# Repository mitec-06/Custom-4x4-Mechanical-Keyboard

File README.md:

# Custom 4x4 Keyboard PCB Design

This project is a custom 4x4 mechanical keyboard PCB featuring USB HID firmware on RP2040, addressable RGB LEDs (SK6812) driven via PIO state machine, rotary encoder brightness control, and HSV color animation functions.

## Functions

### Core Functions

- 16 keys arranged in a 4 x 4 matrix pattern.

- 6 key rollover - up to 6 simultaneous keypresses registered.

- USB HID keyboard output - It can work as a plug-and-play keyboard on any computer.

- Debouncing key detection - Prevents false or double triggers from a mechanical switch bounce.

- Diode per key - Diodes were included for every key in order to prevent ghosting.

### LED Functions
- Idle RGB ripple animation - Outward ripple effect starting from center rings cycling through the entire HSV color spectrum.

- Keypress-reactive LEDS - Animation switches to keypress mode when any key is pressed, returns to idle afterwards.

- Full HSV color transition - Smooth transition between red, orange, yellow, green, cyan, blue, magenta and back.

- Ring based animation - Three concentric rings with slight phase offset creating a ripple appearance.

- Brightness control - Using a rotary encoder, smooth brightness scaling from 0-100% applied uniformly to all LEDs.

- Brightness preserved across all animation modes, whether its idle or a key is being pressed.

### Encoder Functions 

- Clockwise rotation increases brightness, counterclockwise rotation decreases brightness.

- Hardware debouncing edge detection - Prevents any skips when rotating the encoder.

### Hardware Features 

- 3.3V to 5V level shifting for LED data signal via SN74LV1T34

- Daisy-chained SK6812 MINI-E LEDs driven via RP2040 PIO state machine.

- RP2040 PIO state machine - Dedicated programmable Input/Output handles precise WS2812 timing independent of CPU timing.

- WS2812 protocol followed to ensure correct latch reset timing.

- USB powered - single cable for both HID and power communication.

## Timeline

### April 2026 - May 2026

Primarily worked on keyboard research, and drafting the schematic and pcb. Once the pcb was finished, spent some time revising the placement of parts on the board to make sure that there were no shorts or awkward placements that would make assembly difficult.

### May 2026 - June 2026

Ordered the first batch of PCBs from PCBWay, and begun soldering the first prototype, however several hardware bugs prevented the LEDs from functioning properly, causing odd behavior, and allowing only the typing to work.

### June 2026 - July 2026
Managed to get the first four LEDs of the board working, with the other 12 not functioning properly.

Extensively debugged several iterations of the board, ultimately finding that the DIN and DOUT pins on the SK6812 MINI-Es were swapped on the 5th-8th LEDs.

Because the keyboard follows a serpentine transmission of data where the signal of the next LED depends on the signal of the last LED, this broke the sequence for the rest of the LEDs.

Ultimately, the DIN/DOUT pins were finally oriented correctly, and a new batch of PCBs were ordered.

### July 2026 - August 2026

Assembled and soldered the new functioning PCBs, which finally had all 16 LEDs turn on properly. In this time period, the rest of the firmware was added, including the logic for the HSV color transition, the ring-like HSV color animation, the logic for the LED brightness dimming, etc.

In this time period, the case of the PCB was modelled using OnShape, and 3D printed, being assembled towards the end of this project, and ultimately yielding the final keyboard product. :)

## Future Improvements

- Most notably, while assembling/soldering check more frequently whether the parts assembled have the right voltage/behavior using tools such as oscilloscopes or multimeters.

- When hardware debugging, record previous symptoms of the build to ensure that the user assembling the PCB has the full picture, and might not confuse the actual cause of the bug for something else.

- Exercise more caution right before ordering PCBs, ensuring several times that the parts on the PCB have been wired correctly, even if it may pass the Design Rule Check.

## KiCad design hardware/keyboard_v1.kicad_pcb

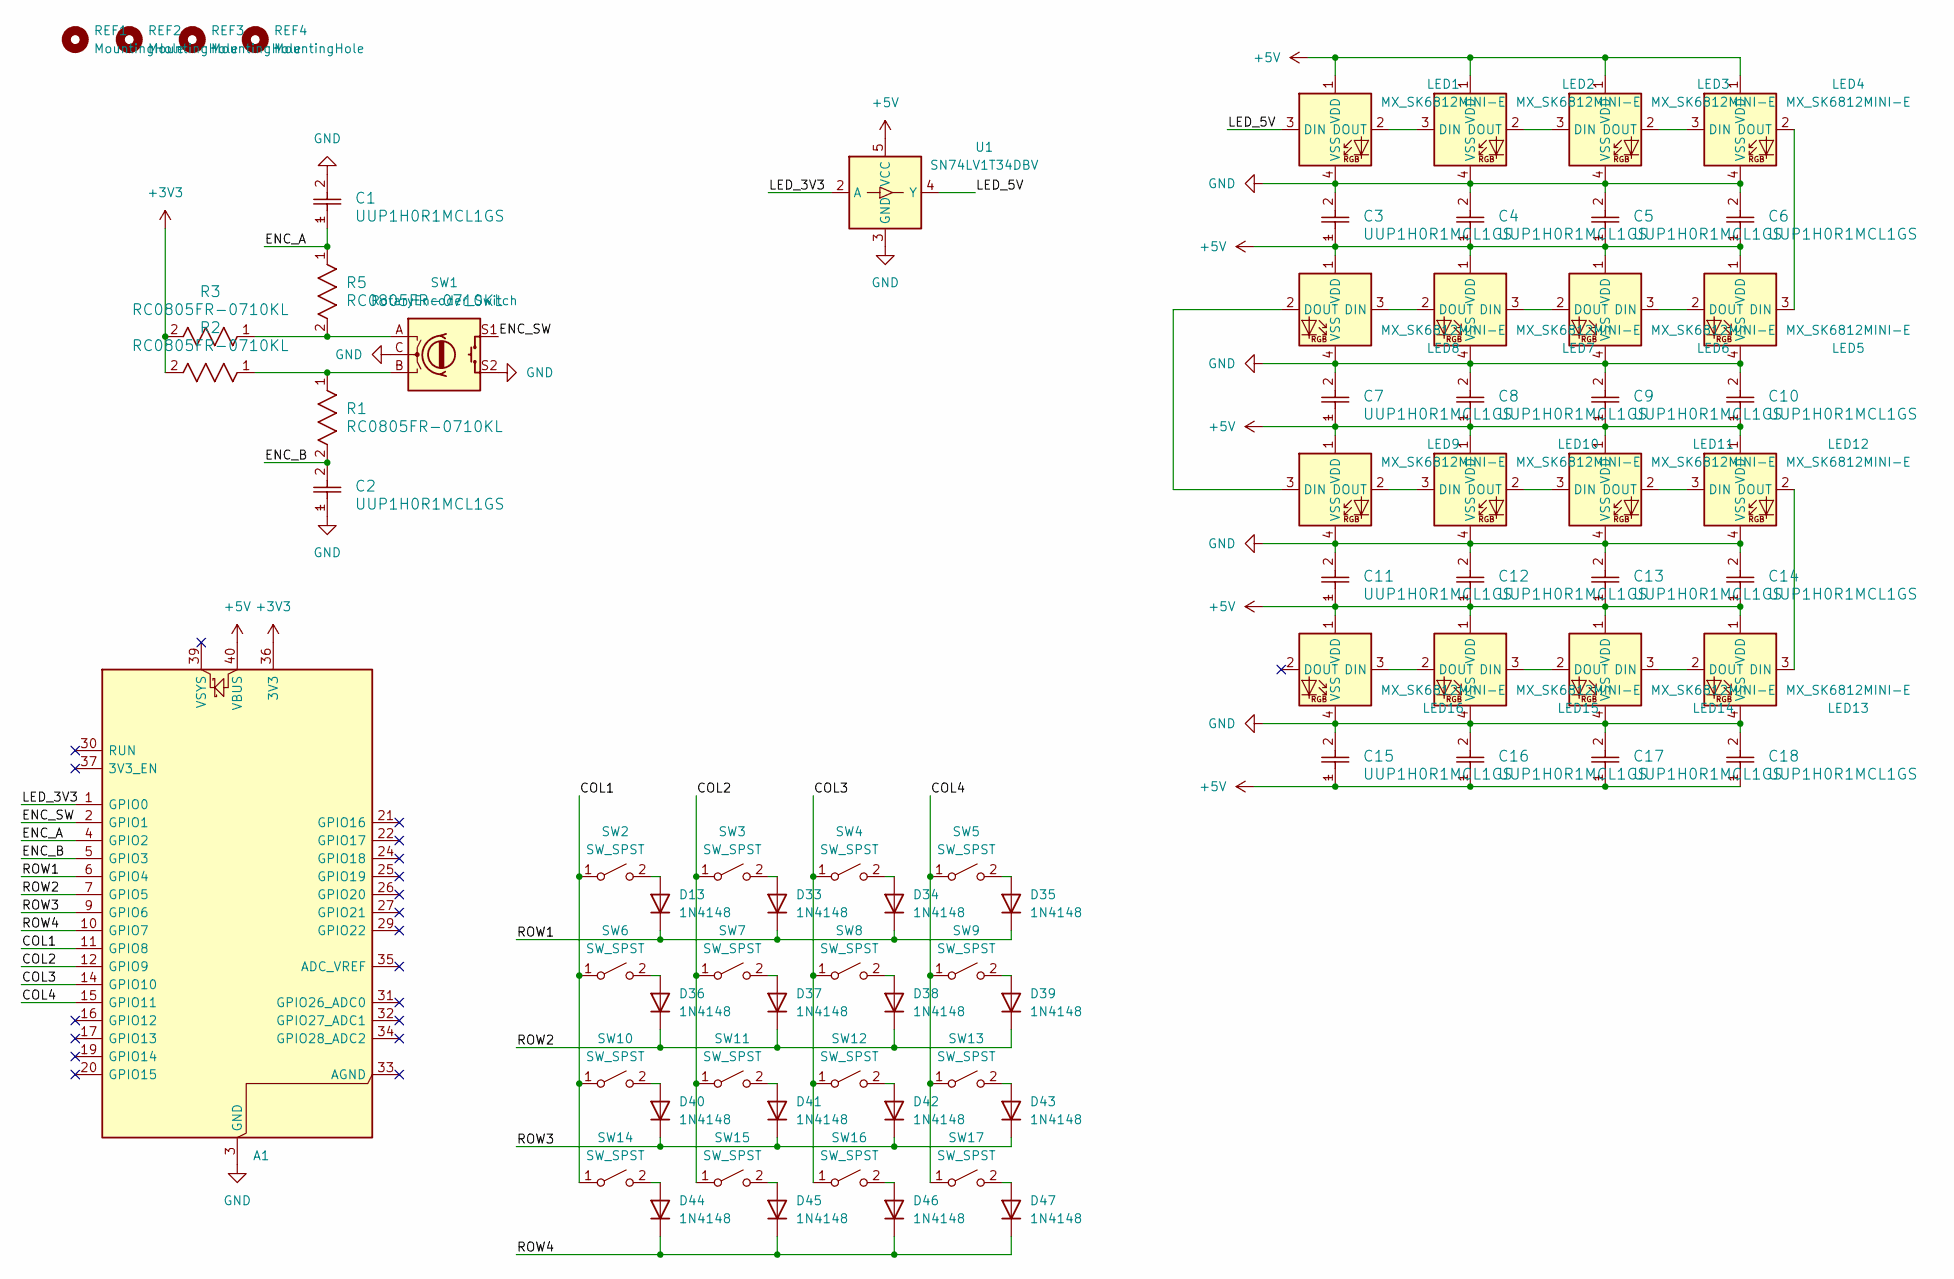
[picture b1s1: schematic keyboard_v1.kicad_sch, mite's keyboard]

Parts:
A1: RaspberryPi_Pico; RaspberryPi_Pico_Common_Unspecified
C1, C2, C3, C4, C5, C6, C7, C8, C9, C10, C11, C12, C13, C14, C15, C16, C17, C18: UUP1H0R1MCL1GS; CAP_UCD_4X5P8_NCH
D13, D33, D34, D35, D36, D37, D38, D39, D40, D41, D42, D43, D44, D45, D46, D47: 1N4148; D_DO-35_SOD27_P7.62mm_Horizontal
LED1, LED2, LED3, LED4, LED5, LED6, LED7, LED8, LED9, LED10, LED11, LED12, LED13, LED14, LED15, LED16: MX_SK6812MINI-E; LED_MX_6028R
R1, R2, R3, R5: RC0805FR-0710KL; RC0805N_YAG
REF1, REF2, REF3, REF4: MountingHole; MountingHole_3.2mm_M3
SW1: RotaryEncoder_Switch; RotaryEncoder_Alps_EC11E-Switch_Vertical_H20mm
SW2, SW3, SW4, SW5, SW6, SW7, SW8, SW9, SW10, SW11, SW12, SW13, SW14, SW15, SW16, SW17: SW_SPST; SW_Cherry_MX_1.00u_PCB
U1: SN74LV1T34DBV; SOT-23-5

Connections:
+3V3: A1.36 (3V3), R2.2, R3.2
+5V: A1.40 (VBUS), C3.1, C4.1, C5.1, C6.1, C7.1, C8.1, C9.1, C10.1, C11.1, C12.1, C13.1, C14.1, C15.1, C16.1, C17.1, C18.1, LED1.1 (VDD), LED2.1 (VDD), LED3.1 (VDD), LED4.1 (VDD), LED5.1 (VDD), LED6.1 (VDD), LED7.1 (VDD), LED8.1 (VDD), LED9.1 (VDD), LED10.1 (VDD), LED11.1 (VDD), LED12.1 (VDD), LED13.1 (VDD), LED14.1 (VDD), LED15.1 (VDD), LED16.1 (VDD), U1.5 (VCC)
/COL1: A1.11 (GPIO8), SW2.1 (A), SW6.1 (A), SW10.1 (A), SW14.1 (A)
/COL2: A1.12 (GPIO9), SW3.1 (A), SW7.1 (A), SW11.1 (A), SW15.1 (A)
/COL3: A1.14 (GPIO10), SW4.1 (A), SW8.1 (A), SW12.1 (A), SW16.1 (A)
/COL4: A1.15 (GPIO11), SW5.1 (A), SW9.1 (A), SW13.1 (A), SW17.1 (A)
/ENC_A: A1.4 (GPIO2), C1.1, R5.1
/ENC_B: A1.5 (GPIO3), C2.2, R1.2
/ENC_SW: A1.2 (GPIO1), SW1.S1
/LED_3V3: A1.1 (GPIO0), U1.2 (A)
/LED_5V: LED1.3 (DIN), U1.4 (Y)
/ROW1: A1.6 (GPIO4), D13.1 (K), D33.1 (K), D34.1 (K), D35.1 (K)
/ROW2: A1.7 (GPIO5), D36.1 (K), D37.1 (K), D38.1 (K), D39.1 (K)
/ROW3: A1.9 (GPIO6), D40.1 (K), D41.1 (K), D42.1 (K), D43.1 (K)
/ROW4: A1.10 (GPIO7), D44.1 (K), D45.1 (K), D46.1 (K), D47.1 (K)
GND: A1.3 (GND), A1.8 (GND), A1.13 (GND), A1.18 (GND), A1.23 (GND), A1.28 (GND), A1.38 (GND), C1.2, C2.1, C3.2, C4.2, C5.2, C6.2, C7.2, C8.2, C9.2, C10.2, C11.2, C12.2, C13.2, C14.2, C15.2, C16.2, C17.2, C18.2, LED1.4 (VSS), LED2.4 (VSS), LED3.4 (VSS), LED4.4 (VSS), LED5.4 (VSS), LED6.4 (VSS), LED7.4 (VSS), LED8.4 (VSS), LED9.4 (VSS), LED10.4 (VSS), LED11.4 (VSS), LED12.4 (VSS), LED13.4 (VSS), LED14.4 (VSS), LED15.4 (VSS), LED16.4 (VSS), SW1.C, SW1.S2, U1.3 (GND)
unnamed: D13.2 (A), SW2.2 (B)
unnamed: D33.2 (A), SW3.2 (B)
unnamed: D34.2 (A), SW4.2 (B)
unnamed: D35.2 (A), SW5.2 (B)
unnamed: D36.2 (A), SW6.2 (B)
unnamed: D37.2 (A), SW7.2 (B)
unnamed: D38.2 (A), SW8.2 (B)
unnamed: D39.2 (A), SW9.2 (B)
unnamed: D40.2 (A), SW10.2 (B)
unnamed: D41.2 (A), SW11.2 (B)
unnamed: D42.2 (A), SW12.2 (B)
unnamed: D43.2 (A), SW13.2 (B)
unnamed: D44.2 (A), SW14.2 (B)
unnamed: D45.2 (A), SW15.2 (B)
unnamed: D46.2 (A), SW16.2 (B)
unnamed: D47.2 (A), SW17.2 (B)
unnamed: LED1.2 (DOUT), LED2.3 (DIN)
unnamed: LED2.2 (DOUT), LED3.3 (DIN)
unnamed: LED3.2 (DOUT), LED4.3 (DIN)
unnamed: LED4.2 (DOUT), LED5.3 (DIN)
unnamed: LED5.2 (DOUT), LED6.3 (DIN)
unnamed: LED6.2 (DOUT), LED7.3 (DIN)
unnamed: LED7.2 (DOUT), LED8.3 (DIN)
unnamed: LED8.2 (DOUT), LED9.3 (DIN)
unnamed: LED9.2 (DOUT), LED10.3 (DIN)
unnamed: LED10.2 (DOUT), LED11.3 (DIN)
unnamed: LED11.2 (DOUT), LED12.3 (DIN)
unnamed: LED12.2 (DOUT), LED13.3 (DIN)
unnamed: LED13.2 (DOUT), LED14.3 (DIN)
unnamed: LED14.2 (DOUT), LED15.3 (DIN)
unnamed: LED15.2 (DOUT), LED16.3 (DIN)
unnamed: R1.1, R2.1, SW1.B
unnamed: R3.1, R5.2, SW1.A

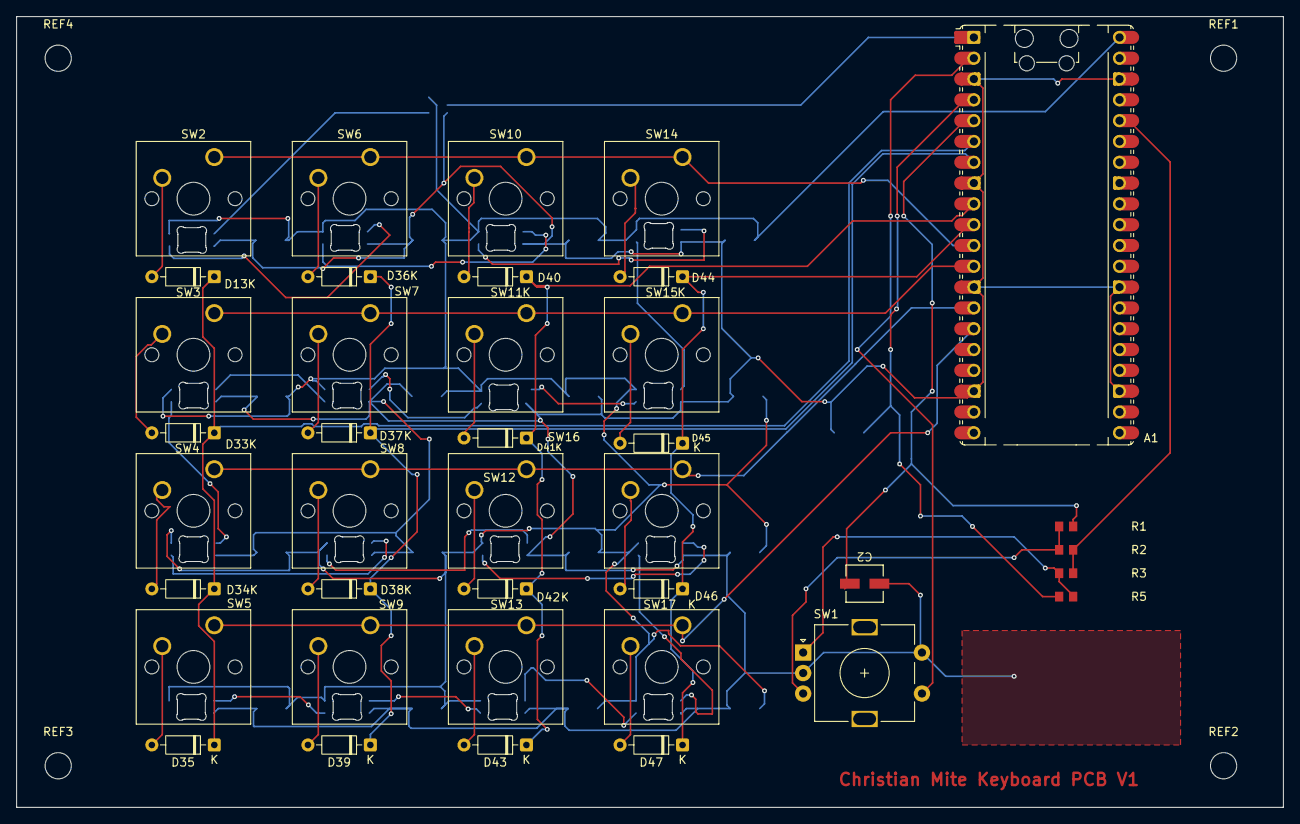
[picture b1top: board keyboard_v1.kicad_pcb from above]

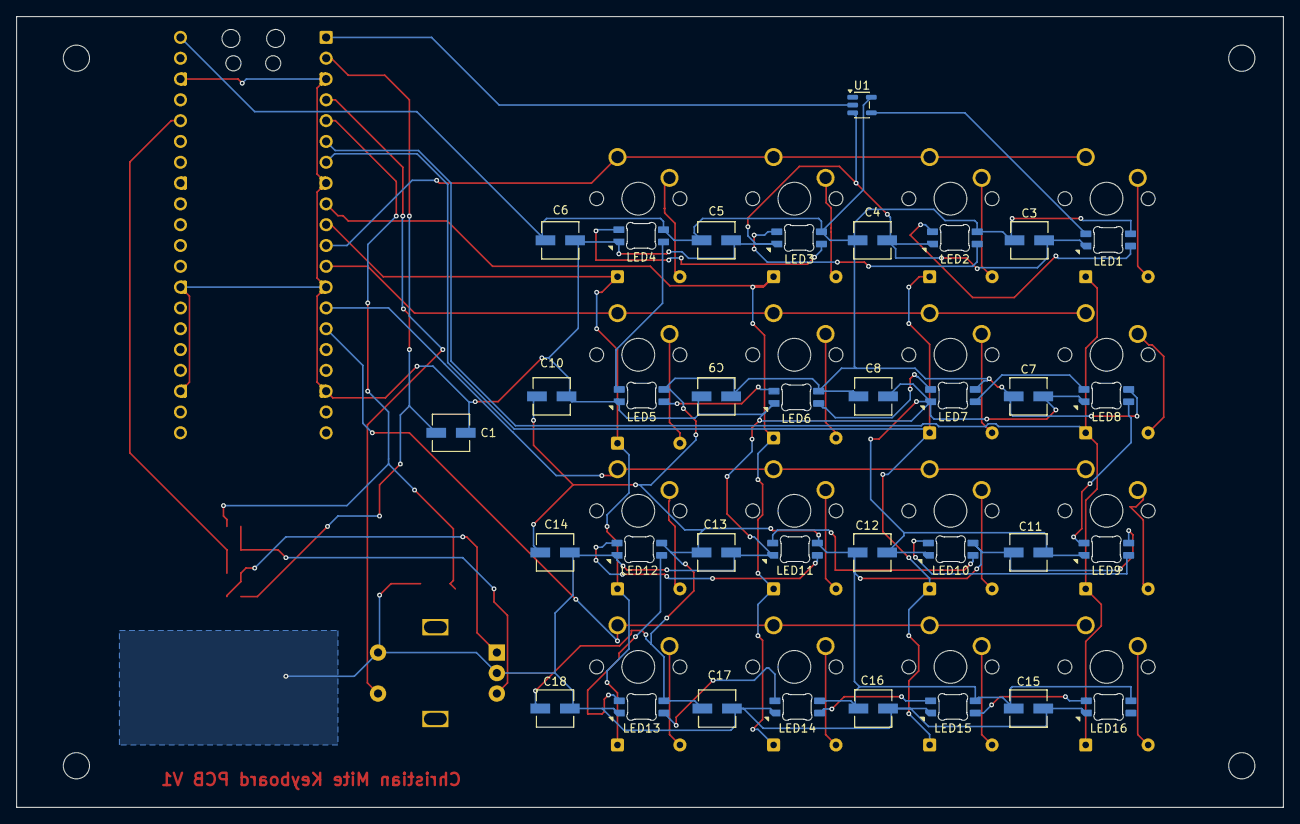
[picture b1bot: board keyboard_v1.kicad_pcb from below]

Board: 2 copper layers, 154.6 x 96.5 mm, 77 parts (34 on the bottom side), 49 nets.

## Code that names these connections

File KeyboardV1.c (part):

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bool led_map[4][4] = {0};
static volatile bool matrix_changed = false;

const uint ENC_SW = 1;
const uint ENC_A = 2;
const uint ENC_B = 3;

#define LED_COUNT 16

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    uint offset = pio_add_program(pio, &ws2812_program);

    // set the pins as GPIO_PWM
    gpio_init(ENC_A);
    gpio_set_dir(ENC_A, GPIO_IN);
    gpio_pull_up(ENC_A);

    gpio_init(ENC_B);
    gpio_set_dir(ENC_B, GPIO_IN);
    gpio_pull_up(ENC_B);

    // redundant since two slices are already shared, but just to get the concept down
    
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
    static bool prev_enc_a = true;

    bool first_state = gpio_get(ENC_A);

    // make sure that ENC_A isint turned on
    if (prev_enc_a && !first_state){
        // 5 ms sleep for debouncing VERY IMPORTANT, WILL NOT RUN PROPERLY OTHERWISE
        sleep_ms(1);
        // checks one last time to make sure that ENC_A isint on
        if (!gpio_get(ENC_A)){
        // gpio_xor_mask(1 << 25); used for testing but pretty useless tbh
        bool other_state = gpio_get(ENC_B);
        // if A is off but B is ON, then its going CW
        if (other_state){
            if (led_brightness == 0){
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
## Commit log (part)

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2026-06-15 Initial code of keyboard, will make it more organized later
